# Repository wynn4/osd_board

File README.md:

# osd_board
This is a custom PCB for interfacing between the Micro MinimOSD and the RCE Tricopter V4.  The board is specifically sized to mount on the back side of the V4 fpv transmitter post.  Components for the board can be found by looking at the attached documents.  The voltage regulator should be a SMD packaged LM2940-5 (LDO 5V regulator) and it needs a 0.47uF 0805 package capacitor on the input and a 33uF 0805 capacitor on the output. For more info, see the LM2940 datasheet.  This is the same regulator and capacitor set that was sold for the tricopter power distribution board from RCExplorer.se.  Note: The 5V regulator portion of this circuit is only needed if you are using the 6V or 8V servo power option on the F3FC frame.  The Micro MinimOSD has no voltage regulation so anything above 5V will toast it.

To fabricate your own PCB simply upload the .brd file to oshpark.com

For complete components list, follow this link: http://www.digikey.com/short/30n53w

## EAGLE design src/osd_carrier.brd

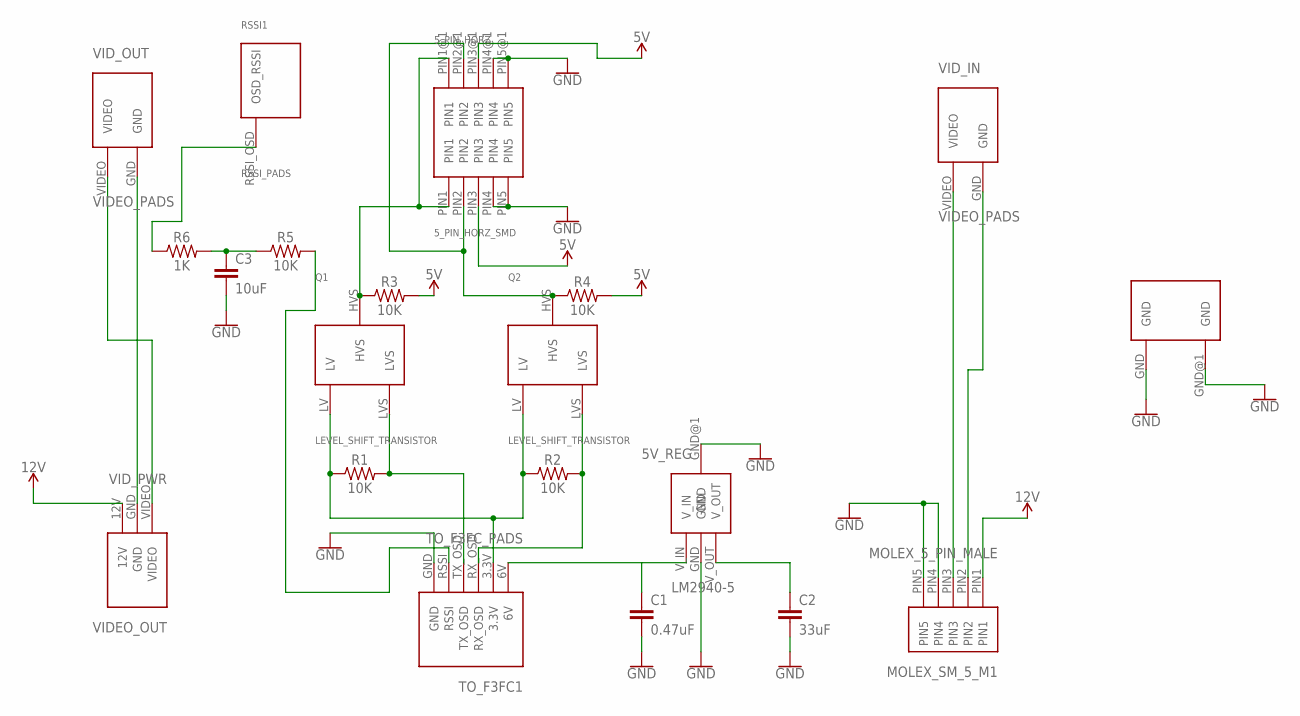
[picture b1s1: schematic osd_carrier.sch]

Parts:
5V_REG: LM2940-5
5_PIN_HORZ: 5_PIN_HORZ_SMD
ANCHOR1: ANCHOR
C1: 0.47uF; 0805
C2: 33uF; 0805
C3: 10uF; 0805
MOLEX_SM_5_M1: MOLEX_5_PIN_MALE
Q1, Q2: LEVEL_SHIFT_TRANSISTOR
R1, R2, R3, R4, R5: 10K; 0603
R6: 1K; 0603
RSSI1: RSSI_PADS
TO_F3FC1: TO_F3FC_PADS
VIDEO_OUT: VID_PWR
VID_IN: VIDEO_PADS
VID_OUT: VIDEO_PADS

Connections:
3.3V: Q1.LV, Q2.LV, R1.1, R2.1, TO_F3FC1.3.3V
5V: 5V_REG.V_OUT, 5_PIN_HORZ.PIN3, 5_PIN_HORZ.PIN3@1 (PIN3), C2.1, R3.2, R4.2
6V: 5V_REG.V_IN, C1.1, TO_F3FC1.6V
12V: MOLEX_SM_5_M1.PIN1, VIDEO_OUT.12V
D4R_II_RSSI: R5.2, TO_F3FC1.RSSI
GND: 5V_REG.GND, 5V_REG.GND@1 (GND), 5_PIN_HORZ.PIN4, 5_PIN_HORZ.PIN4@1 (PIN4), 5_PIN_HORZ.PIN5, 5_PIN_HORZ.PIN5@1 (PIN5), ANCHOR1.GND, ANCHOR1.GND@1, C1.2, C2.2, C3.2, MOLEX_SM_5_M1.PIN2, MOLEX_SM_5_M1.PIN4, MOLEX_SM_5_M1.PIN5, TO_F3FC1.GND, VIDEO_OUT.GND, VID_IN.GND, VID_OUT.GND
unnamed: C3.1, R5.1, R6.2
unnamed: R6.1, RSSI1.RSSI_OSD
RX_OSD_HV: 5_PIN_HORZ.PIN2, 5_PIN_HORZ.PIN2@1 (PIN2), Q2.HVS, R4.1
RX_OSD_LV: Q2.LVS, R2.2, TO_F3FC1.RX_OSD
TX_OSD_HV: 5_PIN_HORZ.PIN1, 5_PIN_HORZ.PIN1@1 (PIN1), Q1.HVS, R3.1
TX_OSD_LV: Q1.LVS, R1.2, TO_F3FC1.TX_OSD
VIDEO_IN: MOLEX_SM_5_M1.PIN3, VID_IN.VIDEO
VID_OUT: VIDEO_OUT.VIDEO, VID_OUT.VIDEO

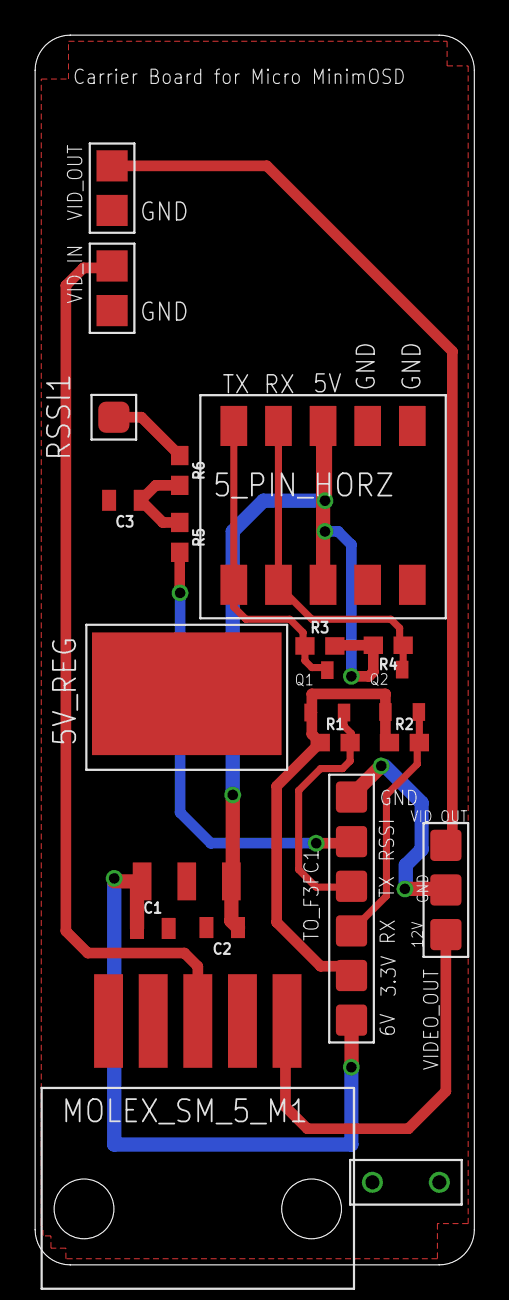
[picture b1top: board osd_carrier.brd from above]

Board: 2 copper layers, 25.0 x 70.0 mm, 20 parts (0 on the bottom side), 14 nets.

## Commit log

2017-07-06 added eagle files
2017-07-06 added more pics
2017-07-06 organized the repo

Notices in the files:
parts and their libraries:
SparkFun-Capacitors: Licensing: Creative Commons ShareAlike 4.0 International - https://creativecommons.org/licenses/by-sa/4.0
